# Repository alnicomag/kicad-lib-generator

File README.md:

kicad-lib-generator
==============

KiCad Schematic Libraries Generator.

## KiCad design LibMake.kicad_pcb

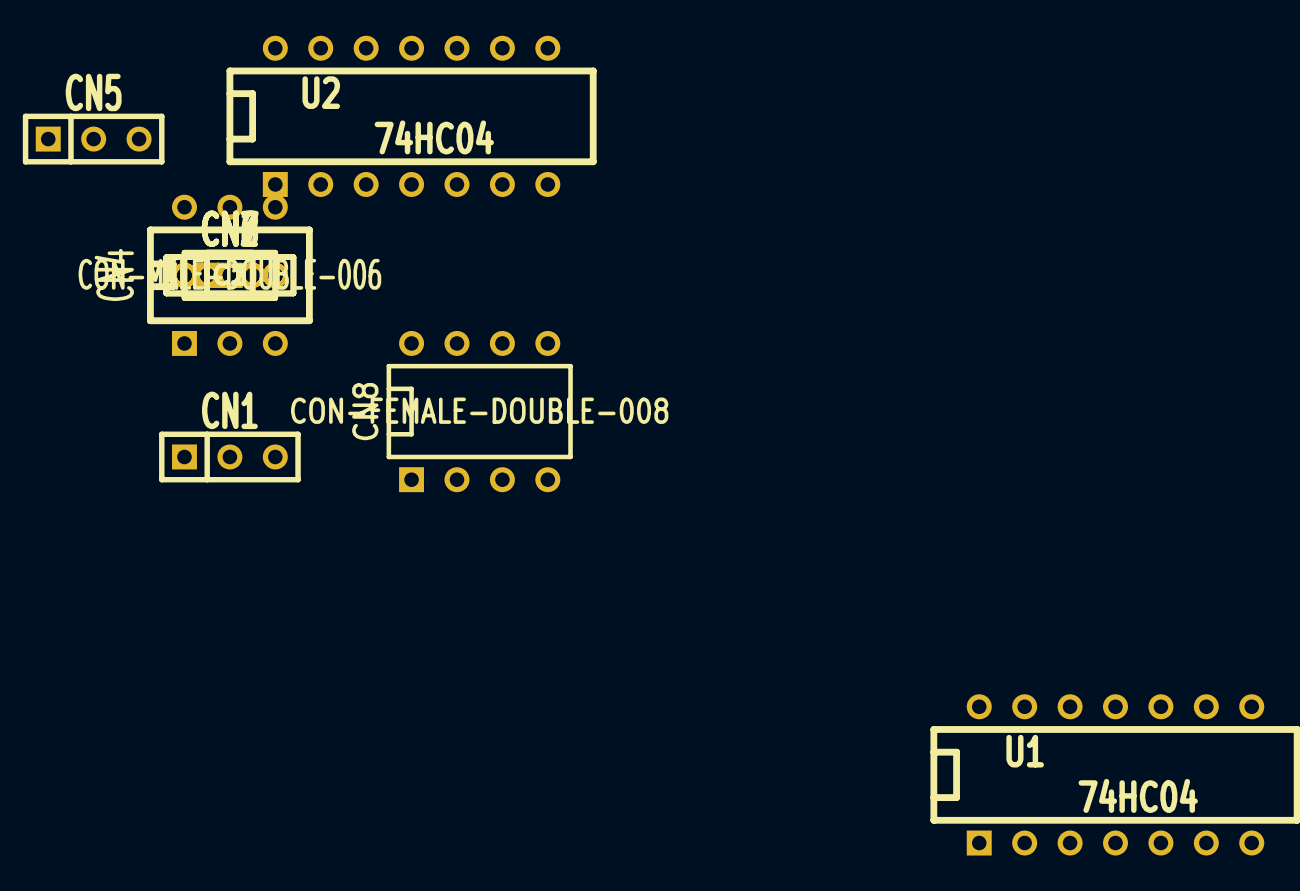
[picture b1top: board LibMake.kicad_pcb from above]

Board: 2 copper layers, 13 parts (0 on the bottom side), 2 nets, no tracks yet.

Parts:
C1: C-TYPE3; C2
C2: C-TYPE2; C2
C3: C-TYPE1; C2
CN1: CON-MALE-SINGLE-003; SIL-3
CN2: CON-MALE-SINGLE-002; SIL-2
CN3: CON-MALE-SINGLE-001; SIL-1
CN4: CON-MALE-DOUBLE-006; DIP-6__300
CN5: CON-FEMALE-SINGLE-003; SIL-3
CN6: CON-FEMALE-SINGLE-002; SIL-2
CN7: CON-FEMALE-SINGLE-001; SIL-1
CN8: CON-FEMALE-DOUBLE-008; DIP-8__300
U1, U2: 74HC04; DIP-14__300

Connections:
GND: U1.7, U2.7
VCC: U1.14, U2.14

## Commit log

2013-03-28 Rename c-type1.lib to C-type1.lib
2013-03-28 Rename c-type2.lib to C-type2.lib
2013-03-28 Rename c-type3.lib to C-type3.lib
2013-03-28 Rename r-type1.lib to R-type1.lib
2013-03-28 Rename r-type2.lib to R-type2.lib
2013-03-28 Add D,fet,jfet,tr
2013-03-28 Change directory
2013-03-28 Rename C-type1.lib to C.lib
2013-03-28 Rename L-type1.lib to L.lib
2013-03-28 Rename R-type1.lib to R.lib
2013-03-28 delete
2013-03-28 project update
2013-03-29 Uodate L.lib
2013-03-29 Add Generator
2013-03-29 Update
    Connector generator is finished.
2013-03-31 Update
    Add supply lib
2013-03-31 Update supply lib
2013-04-16 temp
2013-08-06 日本語を含む.csvをタブ区切りの.txtに変換
2013-08-06 Add .gitignore
2013-08-06 .gitignore is now working
2013-08-06 ディレクトリ変更．
